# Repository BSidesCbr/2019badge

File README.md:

# 2019badge

Nopia 1337

ec0 / Pete

Designed with KiCad EDA and love

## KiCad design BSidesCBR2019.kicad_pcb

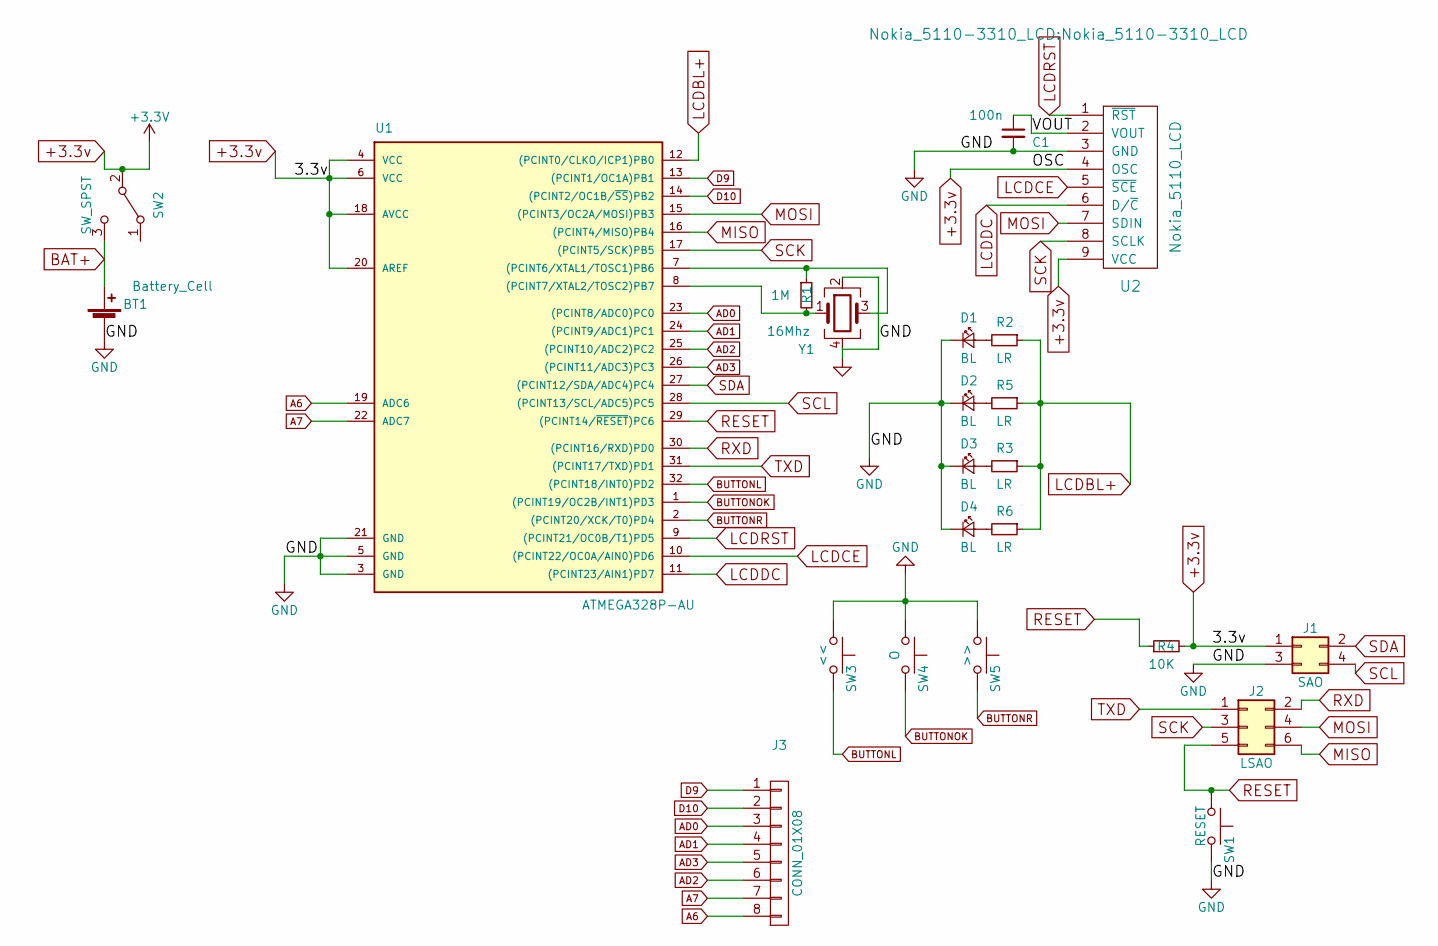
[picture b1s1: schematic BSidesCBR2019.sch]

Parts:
BT1: Battery_Cell; keystone_3008
C1: 100n; C_0805_HandSoldering
D1, D2, D3, D4: BL; LED_0603
J1: SAO; Pin_Header_Straight_2x02_Pitch2.54mm
J2: LSAO; Pin_Header_Straight_2x03_Pitch2.54mm
J3: CONN_01X08; Pin_Header_Straight_1x08_Pitch2.54mm
R1: 1M; R_0805_HandSoldering
R2, R3, R5, R6: LR; R_0805_HandSoldering
R4: 10K; R_0805_HandSoldering
SW1: RESET; SW_SPST_B3SL-1002P
SW2: SW_SPST; SW_SPDT_PCM12
SW3: <<; SW_SPST_B3SL-1002P
SW4: O; SW_SPST_B3SL-1002P
SW5: >>; SW_SPST_B3SL-1002P
U1: ATMEGA328P-AU; QFP80P900X900X120-32N
U2: Nokia_5110_LCD; Nokia_5110-3310_LCD
Y1: 16Mhz; Crystal_SMD_TXC_7M-4pin_3.2x2.5mm_HandSoldering

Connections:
+3.3v: J1.1, R4.2, SW2.2 (B), U1.4 (VCC), U1.6 (VCC), U1.18 (AVCC), U1.20 (AREF), U2.4 (OSC), U2.9 (VCC)
/VOUT: C1.1, U2.2 (VOUT)
A6: J3.8, U1.19 (ADC6)
A7: J3.7, U1.22 (ADC7)
AD0: J3.3, U1.23 ((PCINT8/ADC0)PC0)
AD1: J3.4, U1.24 ((PCINT9/ADC1)PC1)
AD2: J3.6, U1.25 ((PCINT10/ADC2)PC2)
AD3: J3.5, U1.26 ((PCINT11/ADC3)PC3)
BAT+: BT1.1 (+), SW2.3 (C)
BUTTONL: SW3.2, U1.32 ((PCINT18/INT0)PD2)
BUTTONOK: SW4.2, U1.1 ((PCINT19/OC2B/INT1)PD3)
BUTTONR: SW5.2, U1.2 ((PCINT20/XCK/T0)PD4)
D9: J3.1, U1.13 ((PCINT1/OC1A)PB1)
D10: J3.2, U1.14 ((PCINT2/OC1B/~SS~)PB2)
GND: BT1.2 (-), C1.2, D1.1 (K), D2.1 (K), D3.1 (K), D4.1 (K), J1.3, SW1.2, SW3.1, SW4.1, SW5.1, U1.3 (GND), U1.5 (GND), U1.21 (GND), U2.3 (GND), Y1.2, Y1.4
LCDBL+: R2.1, R3.1, R5.1, R6.1, U1.12 ((PCINT0/CLKO/ICP1)PB0)
LCDCE: U1.10 ((PCINT22/OC0A/AIN0)PD6), U2.5 (~SCE)
LCDDC: U1.11 ((PCINT23/AIN1)PD7), U2.6 (D/~C)
LCDRST: U1.9 ((PCINT21/OC0B/T1)PD5), U2.1 (~RST)
MISO: J2.6, U1.16 ((PCINT4/MISO)PB4)
MOSI: J2.4, U1.15 ((PCINT3/OC2A/MOSI)PB3), U2.7 (SDIN)
unnamed: D1.2 (A), R2.2
unnamed: D2.2 (A), R5.2
unnamed: D3.2 (A), R3.2
unnamed: D4.2 (A), R6.2
unnamed: R1.1, U1.7 ((PCINT6/XTAL1/TOSC1)PB6), Y1.3
unnamed: R1.2, U1.8 ((PCINT7/XTAL2/TOSC2)PB7), Y1.1
RESET: J2.5, R4.1, SW1.1, U1.29 ((PCINT14/~RESET~)PC6)
RXD: J2.2, U1.30 ((PCINT16/RXD)PD0)
SCK: J2.3, U1.17 ((PCINT5/SCK)PB5), U2.8 (SCLK)
SCL: J1.4, U1.28 ((PCINT13/SCL/ADC5)PC5)
SDA: J1.2, U1.27 ((PCINT12/SDA/ADC4)PC4)
TXD: J2.1, U1.31 ((PCINT17/TXD)PD1)

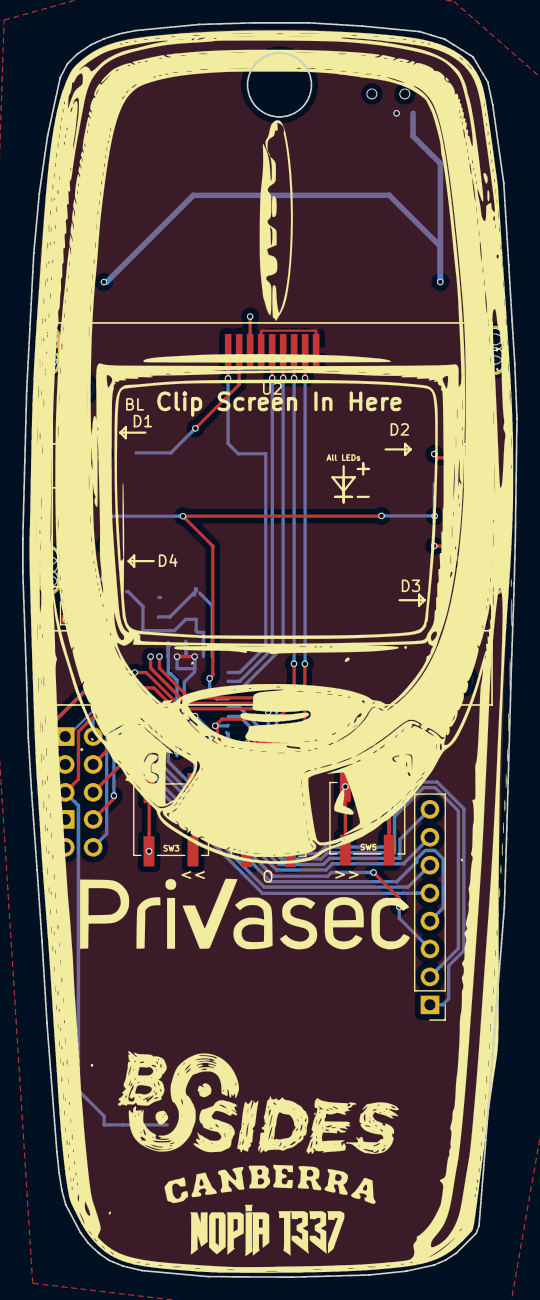
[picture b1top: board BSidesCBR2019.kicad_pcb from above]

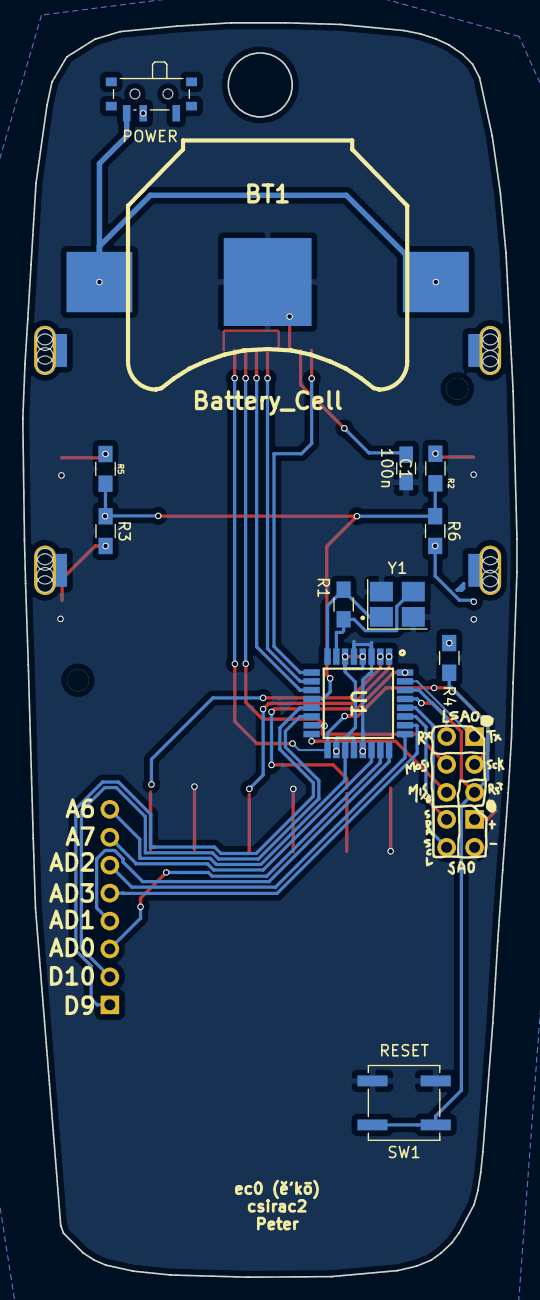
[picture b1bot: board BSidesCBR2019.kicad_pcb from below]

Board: 2 copper layers, 44.9 x 114.1 mm, 23 parts (12 on the bottom side), 33 nets.

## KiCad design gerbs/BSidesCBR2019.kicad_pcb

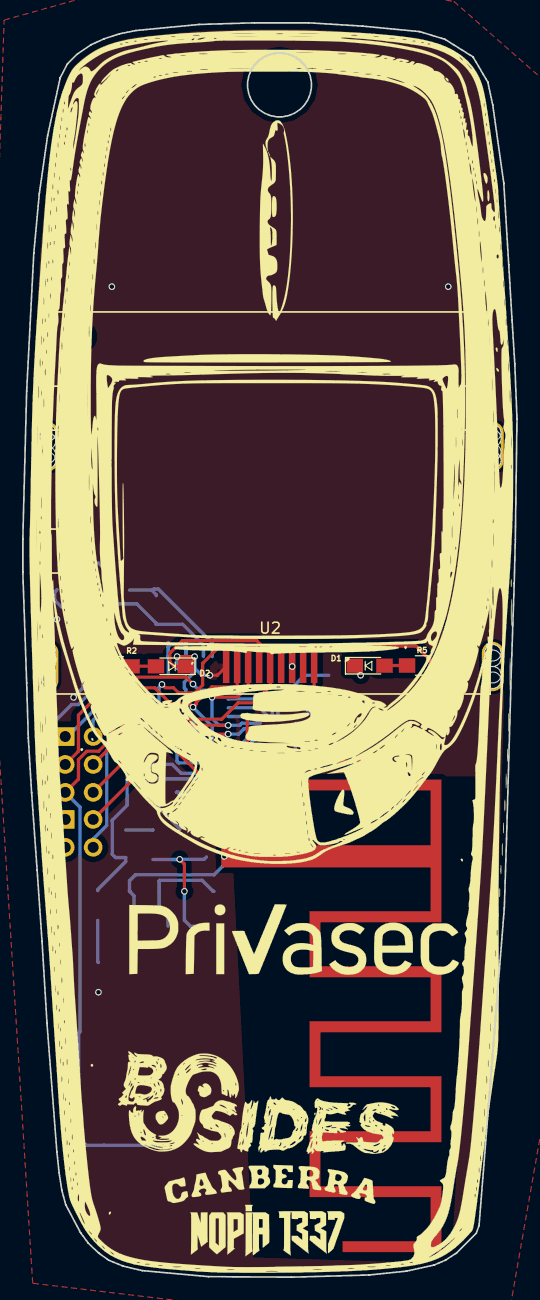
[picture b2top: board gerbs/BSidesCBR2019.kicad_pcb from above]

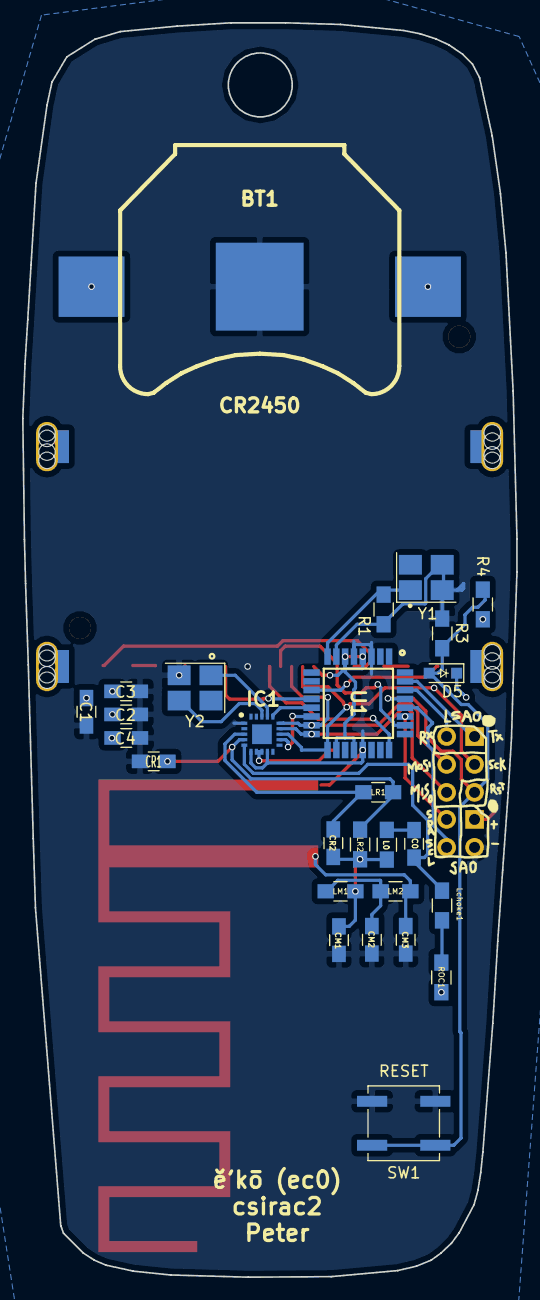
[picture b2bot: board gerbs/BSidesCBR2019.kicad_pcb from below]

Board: 2 copper layers, 44.9 x 114.1 mm, 35 parts (27 on the bottom side), 31 nets.

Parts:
AE1: Antenna_Dipole; ti-dn023-antenna
BT1: CR2450; keystone_3008
C0, C1, C2, C3, C4: C_0805_HandSoldering
CM1, CM2, CM3: C_0805_HandSoldering
CR1, CR2: C_0805_HandSoldering
D1, D2: BL; LED_0805_HandSoldering
D5: 1N4148; D_SOD-323_HandSoldering
IC1: Si4455-B1A-FM; QFN50P300X300X80-21N-D
J1: SAO; Pin_Header_Straight_2x02_Pitch2.54mm
J2: LSAO; Pin_Header_Straight_2x03_Pitch2.54mm
L0: L_0805_HandSoldering
LM1, LM2: L_0805_HandSoldering
LR1, LR2: L_0805_HandSoldering
Lchoke1: L_0805_HandSoldering
R1, R4: 1M; R_0805_HandSoldering
R2, R5: LR; R_0805_HandSoldering
R3: 1K; R_0805_HandSoldering
ROC1: R_0805_HandSoldering
SW1: RESET; SW_SPST_B3SL-1002P
U1: ATMEGA328P-AU; QFP80P900X900X120-32N
U2: Nokia_5110_LCD; Nokia_5110-3310_LCD
Y1: 16Mhz; Crystal_SMD_TXC_7M-4pin_3.2x2.5mm_HandSoldering
Y2: 30Mhz; Crystal_SMD_TXC_7M-4pin_3.2x2.5mm_HandSoldering

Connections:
+3.3v: BT1.1, C1.1, C2.1, C3.1, C4.1, D5.1, IC1.7, IC1.8, J1.1, R4.2, ROC1.1, U1.4, U1.6, U1.18, U1.20, U2.9
/RXN: CR1.2, IC1.4, LR1.1, LR2.2
/RXP: CR2.1, IC1.3, LR1.2
/TXA: C0.1, IC1.5, Lchoke1.2
/XIN: IC1.18, Y2.3
/XOUT: IC1.17, Y2.1
GND: AE1.2, BT1.2, C1.2, C2.2, C3.2, C4.2, CM1.2, CM2.2, CM3.2, CR1.1, D1.1, IC1.1, IC1.6, IC1.9, J1.3, R3.2, SW1.2, U1.3, U1.5, U1.21, U2.3, Y1.2, Y2.2
LCDBL+: R2.2, U1.11
LCDCE: U1.24, U2.5
LCDDC: U1.26, U2.6
LCDRST: U1.12, U2.1
MISO: IC1.14, J2.6, U1.16
MOSI: IC1.15, J2.4, U1.15, U2.7
unnamed: AE1.1, CM3.1, LM2.2
unnamed: C0.2, L0.1
unnamed: CM1.1, CR2.2, L0.2, LM1.1, LR2.1
unnamed: CM2.1, LM1.2, LM2.1
unnamed: D1.2, R5.2
unnamed: D2.1, R5.1
unnamed: D2.2, R2.1
unnamed: Lchoke1.1, ROC1.2
unnamed: R1.1, U1.7, Y1.3
unnamed: R1.2, U1.8, Y1.1
RESET: D5.2, J2.5, R3.1, R4.1, SW1.1, U1.29
RFNIRQ: IC1.12, U1.14
RFNSEL: IC1.16, U1.13
RXD: J2.2, U1.30
SCK: IC1.13, J2.3, U1.17, U2.8
SCL: J1.4, U1.28
SDA: J1.2, U1.27
TXD: J2.1, U1.31

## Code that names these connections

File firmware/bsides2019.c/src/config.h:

#ifndef CONFIG_H_INCLUDED
#define CONFIG_H_INCLUDED

// pin configuration

#define DISPLAY_BL_DDR DDRB
#define DISPLAY_BL_PORT PORTB
#define DISPLAY_BL_PIN PB0

#define DISPLAY_CLK_DDR DDRB
#define DISPLAY_CLK_PORT PORTB
#define DISPLAY_CLK_PIN PB5

#define DISPLAY_DATA_DDR DDRB
#define DISPLAY_DATA_PORT PORTB
#define DISPLAY_DATA_PIN PB3

#define DISPLAY_CS_DDR DDRD
#define DISPLAY_CS_PORT PORTD
#define DISPLAY_CS_PIN PD6

#define DISPLAY_DC_DDR DDRD
#define DISPLAY_DC_PORT PORTD
#define DISPLAY_DC_PIN PD7

#define DISPLAY_RESET_DDR DDRD
#define DISPLAY_RESET_PORT PORTD
#define DISPLAY_RESET_PIN PD5

#define BUTTON_DDR DDRD
#define BUTTON_PORT PORTD
#define BUTTON_LEFT_PIN PD2
#define BUTTON_OK_PIN PD3
#define BUTTON_RIGHT_PIN PD4

#endif /* CONFIG_H_INCLUDED */

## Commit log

2018-11-19 Checkin of v3
2018-11-19 Regen gerbers and update footprint for si4455
2018-11-19 Added each gerber revision, updated with latest version of board designs.
2018-11-19 Added WIP firmware used whilst testing the board
2018-11-25 nopia firmware libs and sketch
2018-11-25 add firmware img resources and script
2018-11-25 silvo juggle concept art
2018-11-26 add tinymenuc
2018-11-28 alpha working
2018-12-01 virtual file system (VFS)
2018-12-08 add schedule (made space for it)
2018-12-08 add dialer
2018-12-09 add imei,id and score qrcode
2018-12-12 Fixes for buttons, added more silkscreen
2018-12-12 button handling improvements
2018-12-15 atmega328p chip pins diagram
2018-12-15 dec prototype mods
2018-12-15 Added footprints and models, v8 gerbs
2018-12-16 fixed PROGMEM usage
2018-12-16 auto imei (no custom flashes)
2018-12-16 dash and signal tidy
2018-12-16 add tinyaes
2018-12-16 menu system cleanup pt1
2018-12-17 menu system cleanup pt2
2018-12-19 more space saving hacks
2018-12-19 add aes crypto for token
2018-12-22 fake base64 & init server-side code
2018-12-22 bugfix token parse
2018-12-27 prod v0.0.1-alpha
2018-12-29 Started on C+u8g2 port. Hardware files verified working.
2019-01-01 csvc cleanup
2019-01-01 font4x6c cleanup
2019-01-01 qrcodegen cleanup
2019-01-01 remove sprintf to save space
2019-01-02 snake cleanup
2019-01-02 tetris cleanup
2019-01-02 tinyaes cleanup
2019-01-02 tinymenuc cleanup
2019-01-02 vfsc cleanup
2019-01-02 vfsc 16-bit file path hash
    (for space)
2019-01-03 vfsc cleanup + obfuscate
2019-01-03 v0.2.0-beta
    working score upload
2019-01-03 v0.2.1-beta
    (prod gpio)
2019-01-03 vgfxc cleanup
2019-01-03 viewerc cleanup
2019-01-03 vintc cleanup
2019-01-03 libraries cleanup
2019-01-04 init server db
2019-01-05 functional server
2019-01-05 retro style for server
2019-01-06 v0.2.2-beta
    bug fix for vfsc header generation
2019-01-06 add vcc power level
2019-01-06 v0.2.3-beta
    crc32 in tokens
2019-01-07 all the strings gone :)
2019-01-08 flags
2019-01-08 fix vfs line endings
2019-01-08 random eeprom
2019-01-08 v0.3.0-beta
    cleanup of all keys and crypto
2019-01-08 random cleanup (no pun)
2019-01-08 add photos
2019-01-08 v0.4.0-beta
    feature complete, waiting for conference details
2019-01-09 v0.4.1-beta
    dont kill eeprom by writing a billion times
2019-01-10 Working on fixing up 3d
2019-01-10 Updated gitignore
2019-01-25 better fake signal
2019-01-25 shaving bytes off images
2019-01-26 2019 schedule + links
2019-01-26 device id spoofing protection
    (weak, but at least its something)
2019-01-27 show VCC with dial code 01
2019-01-27 v1.0.0
    - schedule up-to-date as of 27/01/2019
    - read VCC using dial code 01
    - still need to add battery calibration
2019-01-28 battery calibration
    (still not perfect, but will do)
2019-01-28 more dial codes
2019-01-28 v1.1.0
    - battery calibration
    - dial codes
2019-02-02 v1.2.0
    - nopia.bsidescbr.com.au
    - hhv schedule update
2019-02-02 flashing python script
    - tested with avrisp2
    - tested on windows
2019-03-10 script used to flash badges
2019-03-10 show 1 score per IMEI
2019-03-20 Cleaned up repository
2019-03-20 Add examples
